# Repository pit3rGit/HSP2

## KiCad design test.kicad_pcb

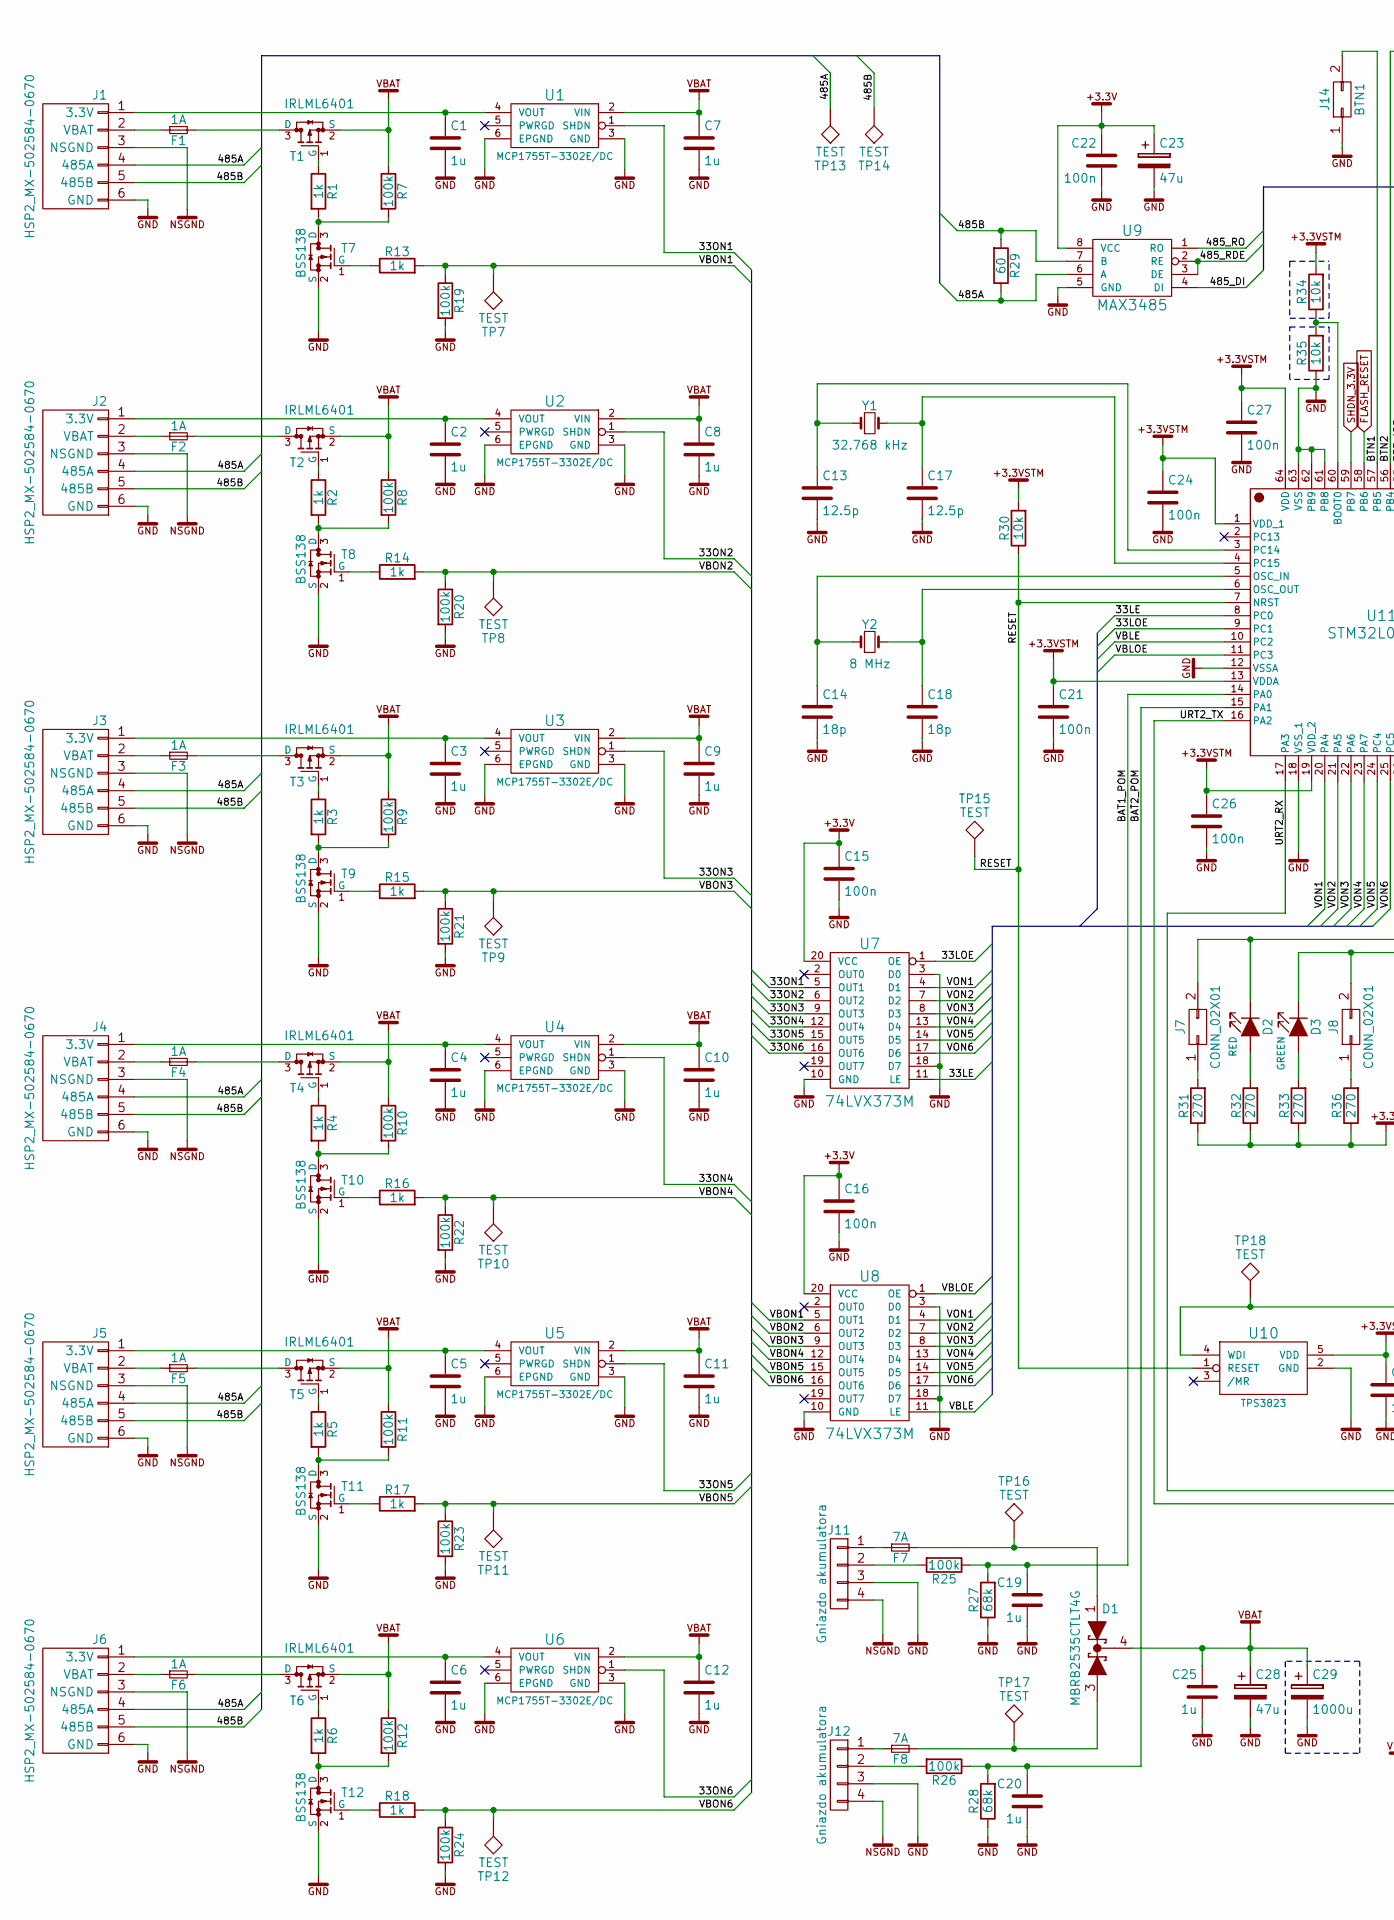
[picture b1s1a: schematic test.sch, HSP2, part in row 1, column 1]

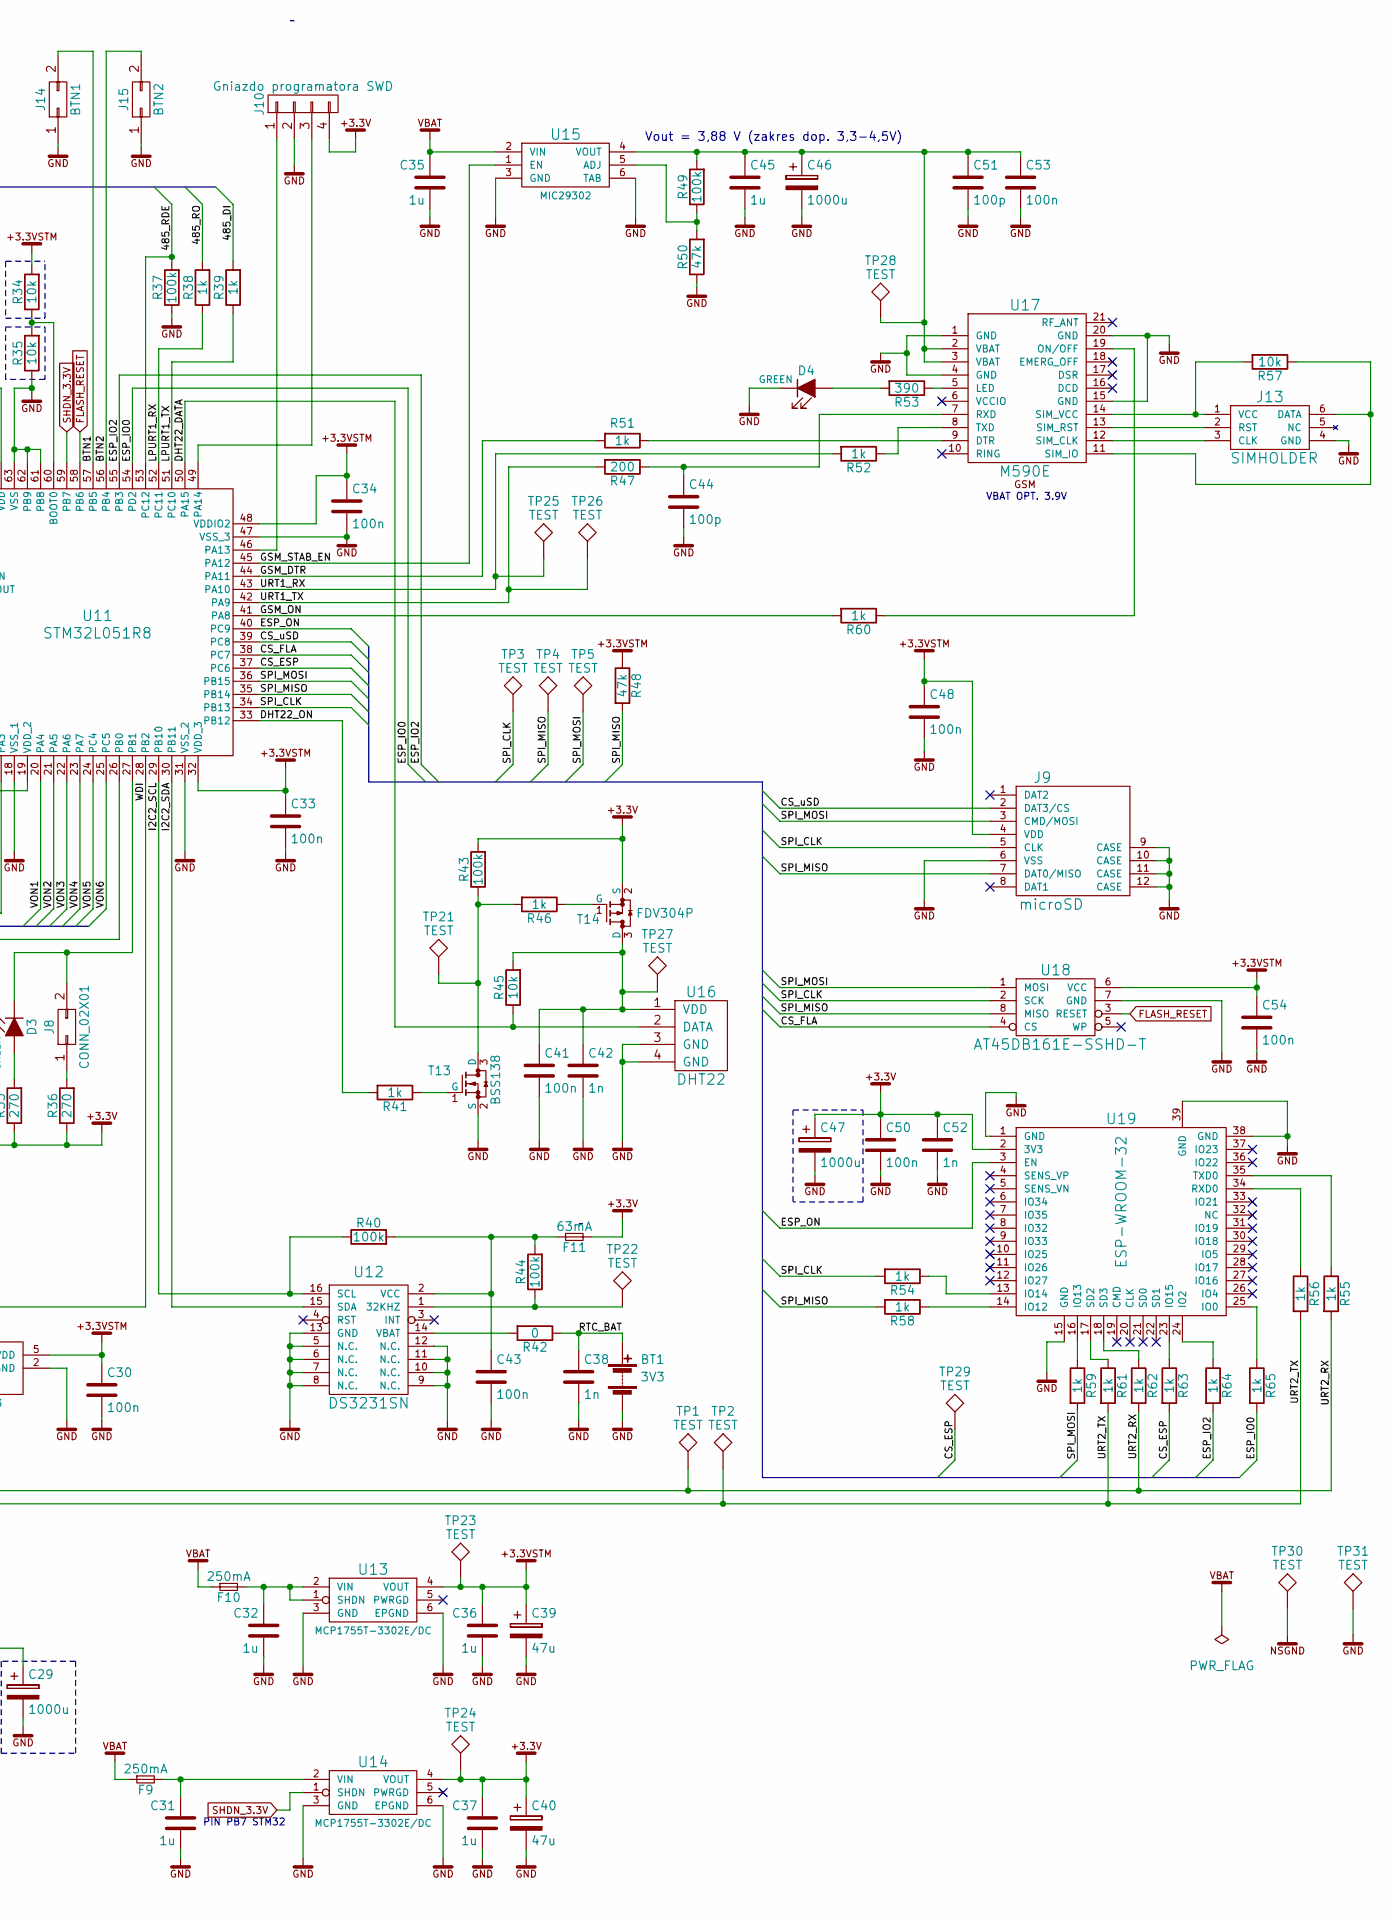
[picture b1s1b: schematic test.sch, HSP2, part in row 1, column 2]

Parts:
BT1: 3V3; CONNFLY_DS1092-13-N8S
C1, C2, C3, C4, C5, C6, C7, C8, C9, C10, C11, C12, C19, C20, C25, C31, C32, C35, C36, C37, C45: 1u; C_0603
C13, C17: 12.5p; C_0603
C14, C18: 18p; C_0603
C15, C16, C21, C22, C24, C26, C27, C30, C33, C34, C41, C43, C48, C50, C53, C54: 100n; C_0603
C23, C28, C39, C40: 47u; 2917in_7343mm
C29, C46, C47: 1000u; CP_Radial_D8.0mm_P3.50mm
C38, C42, C52: 1n; C_0603
C44, C51: 100p; C_0603
D1: MBRB2535CTLT4G; D2PAK
D2: RED; LED_0603
D3, D4: GREEN; LED_0603
F1, F2, F3, F4, F5, F6: 1A; R_0603_HandSoldering
F7, F8: 7A; R_1206_HandSoldering
F9, F10: 250mA; R_1206_HandSoldering
F11: 63mA; SCHURTER_BEZPIECZNIK_OMF63_7.4x3.1
J1, J2, J3, J4, J5, J6: HSP2_MX-502584-0670; MX-502584-0670
J7, J8: CONN_02X01; MX-502584-0270
J9: microSD; ATTEND_uSD_112C_TXAR_R01
J10: Gniazdo programatora SWD; MX-502584-0470
J11, J12: Gniazdo akumulatora; MX-171813-0004
J13: SIMHOLDER; AMPHENOL_SIMHOLDER_C707_10M006_049_2
J14: BTN1; MX-502584-0270
J15: BTN2; MX-502584-0270
R1, R2, R3, R4, R5, R6, R13, R14, R15, R16, R17, R18, R38, R39, R41, R46, R51, R52, R54, R55, R56, R58, R59, R60, R61, R62, R63, R64, R65: 1k; R_0603
R7, R8, R9, R10, R11, R12, R19, R20, R21, R22, R23, R24, R25, R26, R37, R40, R43, R44, R49: 100k; R_0603
R27, R28: 68k; R_0603
R29: 60; R_0603
R30, R34, R35, R45, R57: 10k; R_0603
R31, R32, R33, R36: 270; R_0603
R42: 0; R_0603
R47: 200; R_0603
R48, R50: 47k; R_0603
R53: 390; R_0603
T1, T2, T3, T4, T5, T6: IRLML6401; SOT-23
T7, T8, T9, T10, T11, T12, T13: BSS138; SOT-23
T14: FDV304P; SOT-23
TP1, TP2, TP3, TP4, TP5, TP7, TP8, TP9, TP10, TP11, TP12, TP13, TP14, TP15, TP16, TP17, TP18, TP21, TP22, TP23, TP24, TP25, TP26, TP27, TP28, TP29, TP30, TP31: TEST; Measurement_Point_Round-SMD-Pad_Big
U1, U2, U3, U4, U5, U6, U13, U14: MCP1755T-3302E/DC; SOT-223-6
U7, U8: 74LVX373M; SOIC-20W_7.5x12.8mm_Pitch1.27mm
U9: MAX3485; SO-8
U10: TPS3823; SOT-23-5
U11: STM32L051R8; LQFP-64_10x10mm_Pitch0.5mm
U12: DS3231SN; SO-16-W
U15: MIC29302; TO-263-5_TabPin6
U16: DHT22
U17: M590E
U18: AT45DB161E-SSHD-T; 8-lead_JEDEC_SOIC
U19: ESP-WROOM-32
Y1: 32.768 kHz; Abracon_ABS07
Y2: 8 MHz; Crystal_SMD_HC49-SD_HandSoldering

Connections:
+3.3V: C15.1, C16.1, C22.1, C23.1, C37.1, C40.1, C47.1, C50.1, C52.1, F11.2, J10.4, R31.1, R32.1, R33.1, R36.1, R43.2, T14.2 (S), TP24.1, U7.20 (VCC), U8.20 (VCC), U9.8 (VCC), U14.4 (VOUT), U19.2 (3V3)
+3.3VSTM: C21.1, C24.1, C26.1, C27.1, C30.1, C33.1, C34.1, C36.1, C39.1, C48.1, C54.1, J9.4 (VDD), R30.2, R34.2, R48.1, TP23.1, U10.5 (VDD), U11.1 (VDD_1), U11.13 (VDDA), U11.19 (VDD_2), U11.32 (VDD_3), U11.48 (VDDIO2), U11.64 (VDD), U13.4 (VOUT), U18.6 (VCC)
/33LE: U7.11 (LE), U11.8 (PC0)
/33LOE: U7.1 (OE), U11.9 (PC1)
/33ON1: U1.1 (SHDN), U7.5 (OUT1)
/33ON2: U2.1 (SHDN), U7.6 (OUT2)
/33ON3: U3.1 (SHDN), U7.9 (OUT3)
/33ON4: U4.1 (SHDN), U7.12 (OUT4)
/33ON5: U5.1 (SHDN), U7.15 (OUT5)
/33ON6: U6.1 (SHDN), U7.16 (OUT6)
/485A: J1.4 (485A), J2.4 (485A), J3.4 (485A), J4.4 (485A), J5.4 (485A), J6.4 (485A), R29.1, TP13.1, U9.6 (A)
/485B: J1.5 (485B), J2.5 (485B), J3.5 (485B), J4.5 (485B), J5.5 (485B), J6.5 (485B), R29.2, TP14.1, U9.7 (B)
/485_DI: R39.2, U9.4 (DI)
/485_RDE: R37.2, U9.2 (RE), U9.3 (DE), U11.53 (PC12)
/485_RO: R38.2, U9.1 (RO)
/BAT1_POM: C19.1, R25.1, R27.2, U11.14 (PA0)
/BAT2_POM: C20.1, R26.1, R28.2, U11.15 (PA1)
/BTN1: J14.2, U11.57 (PB5)
/BTN2: J15.2, U11.56 (PB4)
/CS_ESP: R63.2, TP29.1, U11.37 (PC6)
/CS_FLA: U11.38 (PC7), U18.4 (CS)
/CS_uSD: J9.2 (DAT3/CS), U11.39 (PC8)
/DHT22_DATA: R45.1, U11.50 (PA15), U16.2 (DATA)
/DHT22_ON: R41.2, U11.33 (PB12)
/ESP_IO0: R65.2, U11.54 (PD2)
/ESP_IO2: R64.2, U11.55 (PB3)
/ESP_ON: U11.40 (PC9), U19.3 (EN)
/GSM_DTR: R51.2, U11.44 (PA11)
/GSM_ON: R60.2, U11.41 (PA8)
/GSM_STAB_EN: U11.45 (PA12), U15.1 (EN)
/I2C2_SCL: R40.1, U11.29 (PB10), U12.16 (SCL)
/I2C2_SDA: U11.30 (PB11), U12.15 (SDA)
/LPURT1_RX: R38.1, U11.52 (PC11)
/LPURT1_TX: R39.1, U11.51 (PC10)
/RESET: R30.1, TP15.1, U10.1 (RESET), U11.7 (NRST)
/RTC_BAT: BT1.1 (+), C38.1, R42.1
/SPI_CLK: J9.5 (CLK), R54.2, TP3.1, U11.34 (PB13), U18.2 (SCK)
/SPI_MISO: J9.7 (DAT0/MISO), R48.2, R58.2, TP4.1, U11.35 (PB14), U18.8 (MISO)
/SPI_MOSI: J9.3 (CMD/MOSI), R59.2, TP5.1, U11.36 (PB15), U18.1 (MOSI)
/URT1_RX: R52.2, TP25.1, U11.43 (PA10)
/URT1_TX: R47.2, TP26.1, U11.42 (PA9)
/URT2_RX: R55.2, R62.2, TP1.1, U11.17 (PA3)
/URT2_TX: R56.2, R61.2, TP2.1, U11.16 (PA2)
/VBLE: U8.11 (LE), U11.10 (PC2)
/VBLOE: U8.1 (OE), U11.11 (PC3)
/VBON1: R13.2, R19.1, TP7.1, U8.5 (OUT1)
/VBON2: R14.2, R20.1, TP8.1, U8.6 (OUT2)
/VBON3: R15.2, R21.1, TP9.1, U8.9 (OUT3)
/VBON4: R16.2, R22.1, TP10.1, U8.12 (OUT4)
/VBON5: R17.2, R23.1, TP11.1, U8.15 (OUT5)
/VBON6: R18.2, R24.1, TP12.1, U8.16 (OUT6)
/VON1: U7.4 (D1), U8.4 (D1), U11.20 (PA4)
/VON2: U7.7 (D2), U8.7 (D2), U11.21 (PA5)
/VON3: U7.8 (D3), U8.8 (D3), U11.22 (PA6)
/VON4: U7.13 (D4), U8.13 (D4), U11.23 (PA7)
/VON5: U7.14 (D5), U8.14 (D5), U11.24 (PC4)
/VON6: U7.17 (D6), U8.17 (D6), U11.25 (PC5)
/WDI: TP18.1, U10.4 (WDI), U11.28 (PB2)
FLASH_RESET: U11.58 (PB6), U18.3 (RESET)
GND: BT1.2 (-), C1.2, C2.2, C3.2, C4.2, C5.2, C6.2, C7.2, C8.2, C9.2, C10.2, C11.2, C12.2, C13.2, C14.2, C15.2, C16.2, C17.2, C18.2, C19.2, C20.2, C21.2, C22.2, C23.2, C24.2, C25.2, C26.2, C27.2, C28.2, C29.2, C30.2, C31.2, C32.2, C33.2, C34.2, C35.2, C36.2, C37.2, C38.2, C39.2, C40.2, C41.2, C42.2, C43.2, C44.2, C45.2, C46.2, C47.2, C48.2, C50.2, C51.2, C52.2, C53.2, C54.2, D4.1 (K), J1.6 (GND), J2.6 (GND), J3.6 (GND), J4.6 (GND), J5.6 (GND), J6.6 (GND), J9.6 (VSS), J9.9 (CASE), J9.10 (CASE), J9.11 (CASE), J9.12 (CASE), J10.2, J11.3, J12.3, J13.4 (GND), J14.1, J15.1, R19.2, R20.2, R21.2, R22.2, R23.2, R24.2, R27.1, R28.1, R35.1, R37.1, R50.1, T7.2 (S), T8.2 (S), T9.2 (S), T10.2 (S), T11.2 (S), T12.2 (S), T13.2 (S), TP31.1, U1.3 (GND), U1.6 (EPGND), U2.3 (GND), U2.6 (EPGND), U3.3 (GND), U3.6 (EPGND), U4.3 (GND), U4.6 (EPGND), U5.3 (GND), U5.6 (EPGND), U6.3 (GND), U6.6 (EPGND), U7.3 (D0), U7.10 (GND), U7.18 (D7), U8.3 (D0), U8.10 (GND), U8.18 (D7), U9.5 (GND), U10.2 (GND), U11.12 (VSSA), U11.18 (VSS_1), U11.31 (VSS_2), U11.47 (VSS_3), U11.61 (PB8), U11.62 (PB9), U11.63 (VSS), U12.5 (N.C.), U12.6 (N.C.), U12.7 (N.C.), U12.8 (N.C.), U12.9 (N.C.), U12.10 (N.C.), U12.11 (N.C.), U12.12 (N.C.), U12.13 (GND), U13.3 (GND), U13.6 (EPGND), U14.3 (GND), U14.6 (EPGND), U15.3 (GND), U15.6 (TAB), U16.3 (GND), U16.4 (GND), U17.1 (GND), U17.4 (GND), U17.15 (GND), U17.20 (GND), U18.7 (GND), U19.1 (GND), U19.15 (GND), U19.38 (GND), U19.39 (GND)
unnamed: C1.1, J1.1 (3.3V), U1.4 (VOUT)
unnamed: C2.1, J2.1 (3.3V), U2.4 (VOUT)
unnamed: C3.1, J3.1 (3.3V), U3.4 (VOUT)
unnamed: C4.1, J4.1 (3.3V), U4.4 (VOUT)
unnamed: C5.1, J5.1 (3.3V), U5.4 (VOUT)
unnamed: C6.1, J6.1 (3.3V), U6.4 (VOUT)
unnamed: C13.1, U11.3 (PC14), Y1.1
unnamed: C14.1, U11.5 (OSC_IN), Y2.1
unnamed: C17.1, U11.4 (PC15), Y1.2
unnamed: C18.1, U11.6 (OSC_OUT), Y2.2
unnamed: C31.1, F9.2, U14.2 (VIN)
unnamed: C32.1, F10.2, U13.1 (SHDN), U13.2 (VIN)
unnamed: C41.1, C42.1, R45.2, T14.3 (D), TP27.1, U16.1 (VDD)
unnamed: C43.1, F11.1, R40.2, R44.2, U12.2 (VCC)
unnamed: C44.1, R47.1, U17.7 (RXD)
unnamed: C45.1, C46.1, C51.1, C53.1, R49.2, TP28.1, U15.4 (VOUT), U17.2 (VBAT), U17.3 (VBAT)
unnamed: D1.1 (A), F7.2, TP16.1
unnamed: D1.3 (A), F8.2, TP17.1
unnamed: D2.1 (K), J7.2, U11.26 (PB0)
unnamed: D2.2 (A), R32.2
unnamed: D3.1 (K), J8.2, U11.27 (PB1)
unnamed: D3.2 (A), R33.2
unnamed: D4.2 (A), R53.2
unnamed: F1.1, J1.2 (VBAT)
unnamed: F1.2, T1.3 (D)
unnamed: F2.1, J2.2 (VBAT)
unnamed: F2.2, T2.3 (D)
unnamed: F3.1, J3.2 (VBAT)
unnamed: F3.2, T3.3 (D)
unnamed: F4.1, J4.2 (VBAT)
unnamed: F4.2, T4.3 (D)
unnamed: F5.1, J5.2 (VBAT)
unnamed: F5.2, T5.3 (D)
unnamed: F6.1, J6.2 (VBAT)
unnamed: F6.2, T6.3 (D)
unnamed: F7.1, J11.1
unnamed: F8.1, J12.1
unnamed: J7.1, R31.2
unnamed: J8.1, R36.2
unnamed: J10.1, U11.46 (PA13)
unnamed: J10.3, U11.49 (PA14)
unnamed: J11.2, R25.2
unnamed: J12.2, R26.2
unnamed: J13.1 (VCC), R57.2, U17.14 (SIM_VCC)
unnamed: J13.2 (RST), U17.13 (SIM_RST)
unnamed: J13.3 (CLK), U17.12 (SIM_CLK)
unnamed: J13.6 (DATA), R57.1, U17.11 (SIM_IO)
unnamed: R1.1, T1.1 (G)
unnamed: R1.2, R7.2, T7.3 (D)
unnamed: R2.1, T2.1 (G)
unnamed: R2.2, R8.2, T8.3 (D)
unnamed: R3.1, T3.1 (G)
unnamed: R3.2, R9.2, T9.3 (D)
unnamed: R4.1, T4.1 (G)
unnamed: R5.1, T5.1 (G)
unnamed: R6.1, T6.1 (G)
unnamed: R4.2, R10.2, T10.3 (D)
unnamed: R5.2, R11.2, T11.3 (D)
unnamed: R6.2, R12.2, T12.3 (D)
unnamed: R13.1, T7.1 (G)
unnamed: R14.1, T8.1 (G)
unnamed: R15.1, T9.1 (G)
unnamed: R16.1, T10.1 (G)
unnamed: R17.1, T11.1 (G)
unnamed: R18.1, T12.1 (G)
unnamed: R34.1, R35.2, U11.60 (BOOT0)
unnamed: R41.1, T13.1 (G)
unnamed: R42.2, U12.14 (VBAT)
unnamed: R43.1, R46.2, T13.3 (D), TP21.1
unnamed: R44.1, TP22.1, U12.1 (32KHZ)
unnamed: R46.1, T14.1 (G)
unnamed: R49.1, R50.2, U15.5 (ADJ)
unnamed: R51.1, U17.9 (DTR)
unnamed: R52.1, U17.8 (TXD)
unnamed: R53.1, U17.5 (LED)
unnamed: R54.1, U19.13 (IO14)
unnamed: R55.1, U19.35 (TXD0)
unnamed: R56.1, U19.34 (RXD0)
unnamed: R58.1, U19.14 (IO12)
unnamed: R59.1, U19.16 (IO13)
unnamed: R60.1, U17.19 (ON/OFF)
unnamed: R61.1, U19.17 (SD2)
unnamed: R62.1, U19.18 (SD3)
unnamed: R63.1, U19.23 (IO15)
unnamed: R64.1, U19.24 (IO2)
unnamed: R65.1, U19.25 (IO0)
SHDN_3.3V: U11.59 (PB7), U14.1 (SHDN)
VBAT: C7.1, C8.1, C9.1, C10.1, C11.1, C12.1, C25.1, C28.1, C29.1, C35.1, D1.4 (K), F9.1, F10.1, R7.1, R8.1, R9.1, R10.1, R11.1, R12.1, T1.2 (S), T2.2 (S), T3.2 (S), T4.2 (S), T5.2 (S), T6.2 (S), U1.2 (VIN), U2.2 (VIN), U3.2 (VIN), U4.2 (VIN), U5.2 (VIN), U6.2 (VIN), U15.2 (VIN)
~: J1.3 (NSGND), J2.3 (NSGND), J3.3 (NSGND), J4.3 (NSGND), J5.3 (NSGND), J6.3 (NSGND), J11.4, J12.4, TP30.1

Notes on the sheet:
VBAT OPT. 3.9V
Vout = 3,88 V (zakres dop. 3,3-4,5V)
PIN PB7 STM32

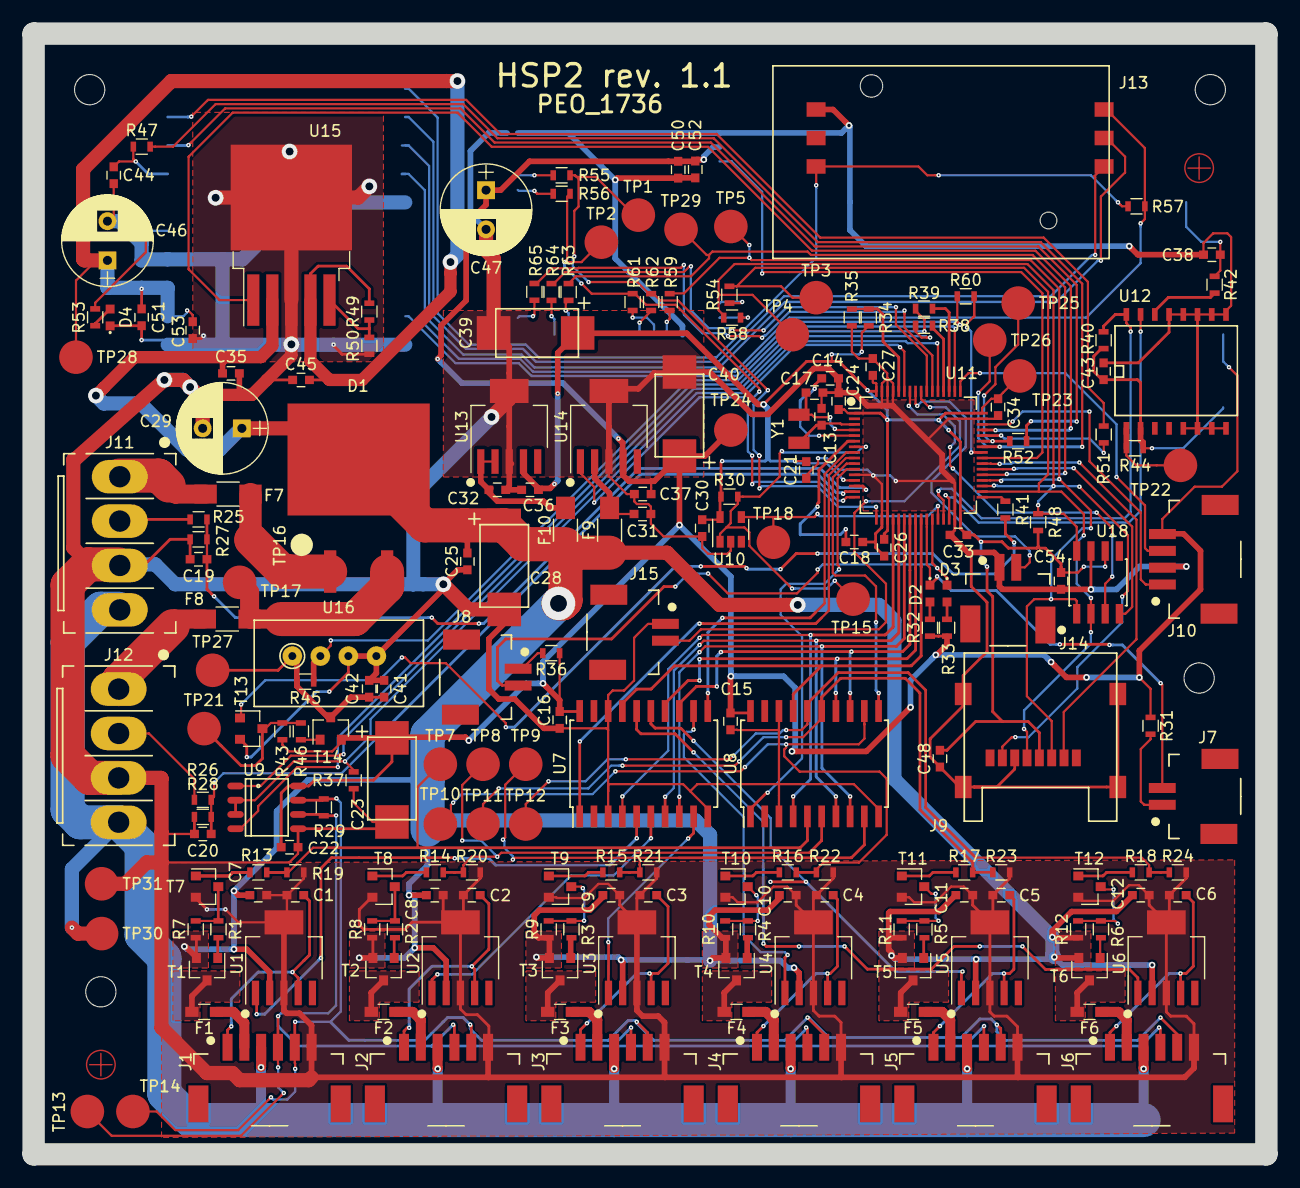
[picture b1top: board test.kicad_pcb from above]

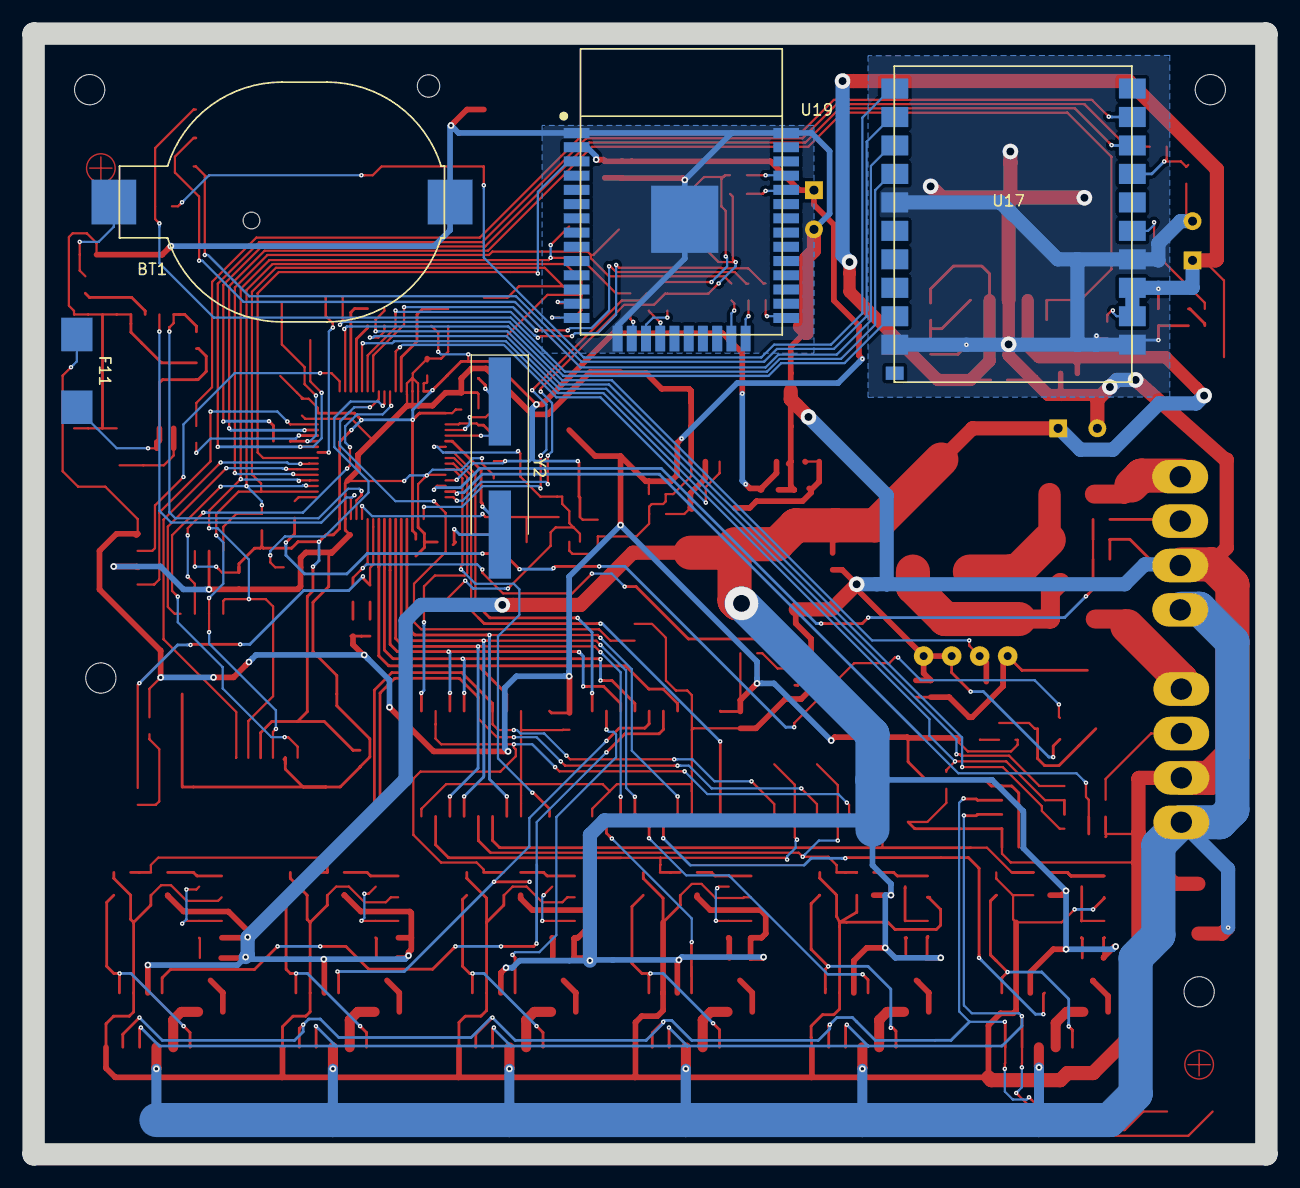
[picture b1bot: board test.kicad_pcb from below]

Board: 2 copper layers, 110.0 x 100.0 mm, 212 parts (5 on the bottom side), 149 nets.

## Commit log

2017-03-14 img14
2017-03-15 img15
2017-03-15 dom15
2017-03-16 img16
2017-03-22 dom22
2017-05-25 laptop
2017-06-01 stary IMG last
2017-06-01 Dodałem układ DHT22
2017-06-01 dodano stab gsmale jest do poprawy
2017-06-02 nowe symbole tranzystorow
2017-06-04 wlasciwy stab dla gsm
2017-06-05 Zmiana ster. wejsciami i drugi gn acu
2017-06-05 dodana dioda i przesuniecia w schemacie
2017-06-06 dodatkowe pliki z dokumentacja
2017-06-06 dodano część footprintów i TPS3823
2017-06-12 nie pamietam
2017-06-12 wersja rev. 1.0
2017-06-13 proba BOK i footprinty
2017-06-13 dodałem niektóre footprinty
2017-06-18 nowe footprinty
2017-06-20 dodałem MAX3485
2017-06-23 footprint M590E
2017-06-26 dodałem footprint do ESP-07
2017-06-27 footp
2017-06-30 koniec czerwca
2017-07-10 zmiana procesora na STM32L051R8
2017-07-10 dodany footprint do stm32
2017-07-11 prace przy simholder
2017-07-12 +zmiany prz uSD
2017-07-13 zmiana gniazd modulów
2017-07-13 zmiana gniazd
2017-07-17 +footprinty zlacz i 3.3VSTM
2017-07-17 poprawa footprintu stab3.3
2017-07-18 rysowanie PCB
2017-07-21 łączenie ścieżek pcb
2017-07-23 rutowanie pcb
2017-07-24 sprawdzanie drc pcb
2017-07-25 mindmapa
2017-07-26 +creo, po naprawie w pracy
2017-07-27 +creo-weipu +zmiana dht22 i c1000
2017-07-28 +dht22 3d +mbr 3d -pliki posprzątane
2017-07-28 +nowe modele 3d. Niedokończone routowanie dth22 w innym miejscu
2017-07-30 routowanie dht22 w nowym miejscu
2017-07-31 przesunięcie karty sim i cr2032
2017-08-03 cap 3d skala +2xGSM rez
2017-08-09 +tp1 tp2 zmieniono strefy miedzi
2017-08-11 ustalanie kosztorysu
2017-08-18 +kosztorys
2017-08-21 zm kosztorys
2017-08-22 podmiana wifi na esp32
2017-08-25 routowanie nowego esp
2017-08-27 routowanie esp32
2017-08-28 esp32 i btn zrutowanie calkowicie
2017-08-29 uzupelnienie do poprzedniego commitu
2017-09-05 wersja final, freeze wyslana do technoservice
2017-09-05 zmiana flash
2017-09-05 poprawione przelotki i ścieżki
2017-09-06 wyslane do produkcji
2018-01-10 Przed ukladaniem PCB
2018-01-18 pierwszy program + CubeMX
2018-01-18 jakas stara zmiana mind mapy
2018-01-18 program hsp2 LL LPUART poczatek
